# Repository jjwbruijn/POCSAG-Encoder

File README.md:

POCSAG-Encoder
==============
For more info, see http://jelmerbruijn.nl/pocsag-encoder/

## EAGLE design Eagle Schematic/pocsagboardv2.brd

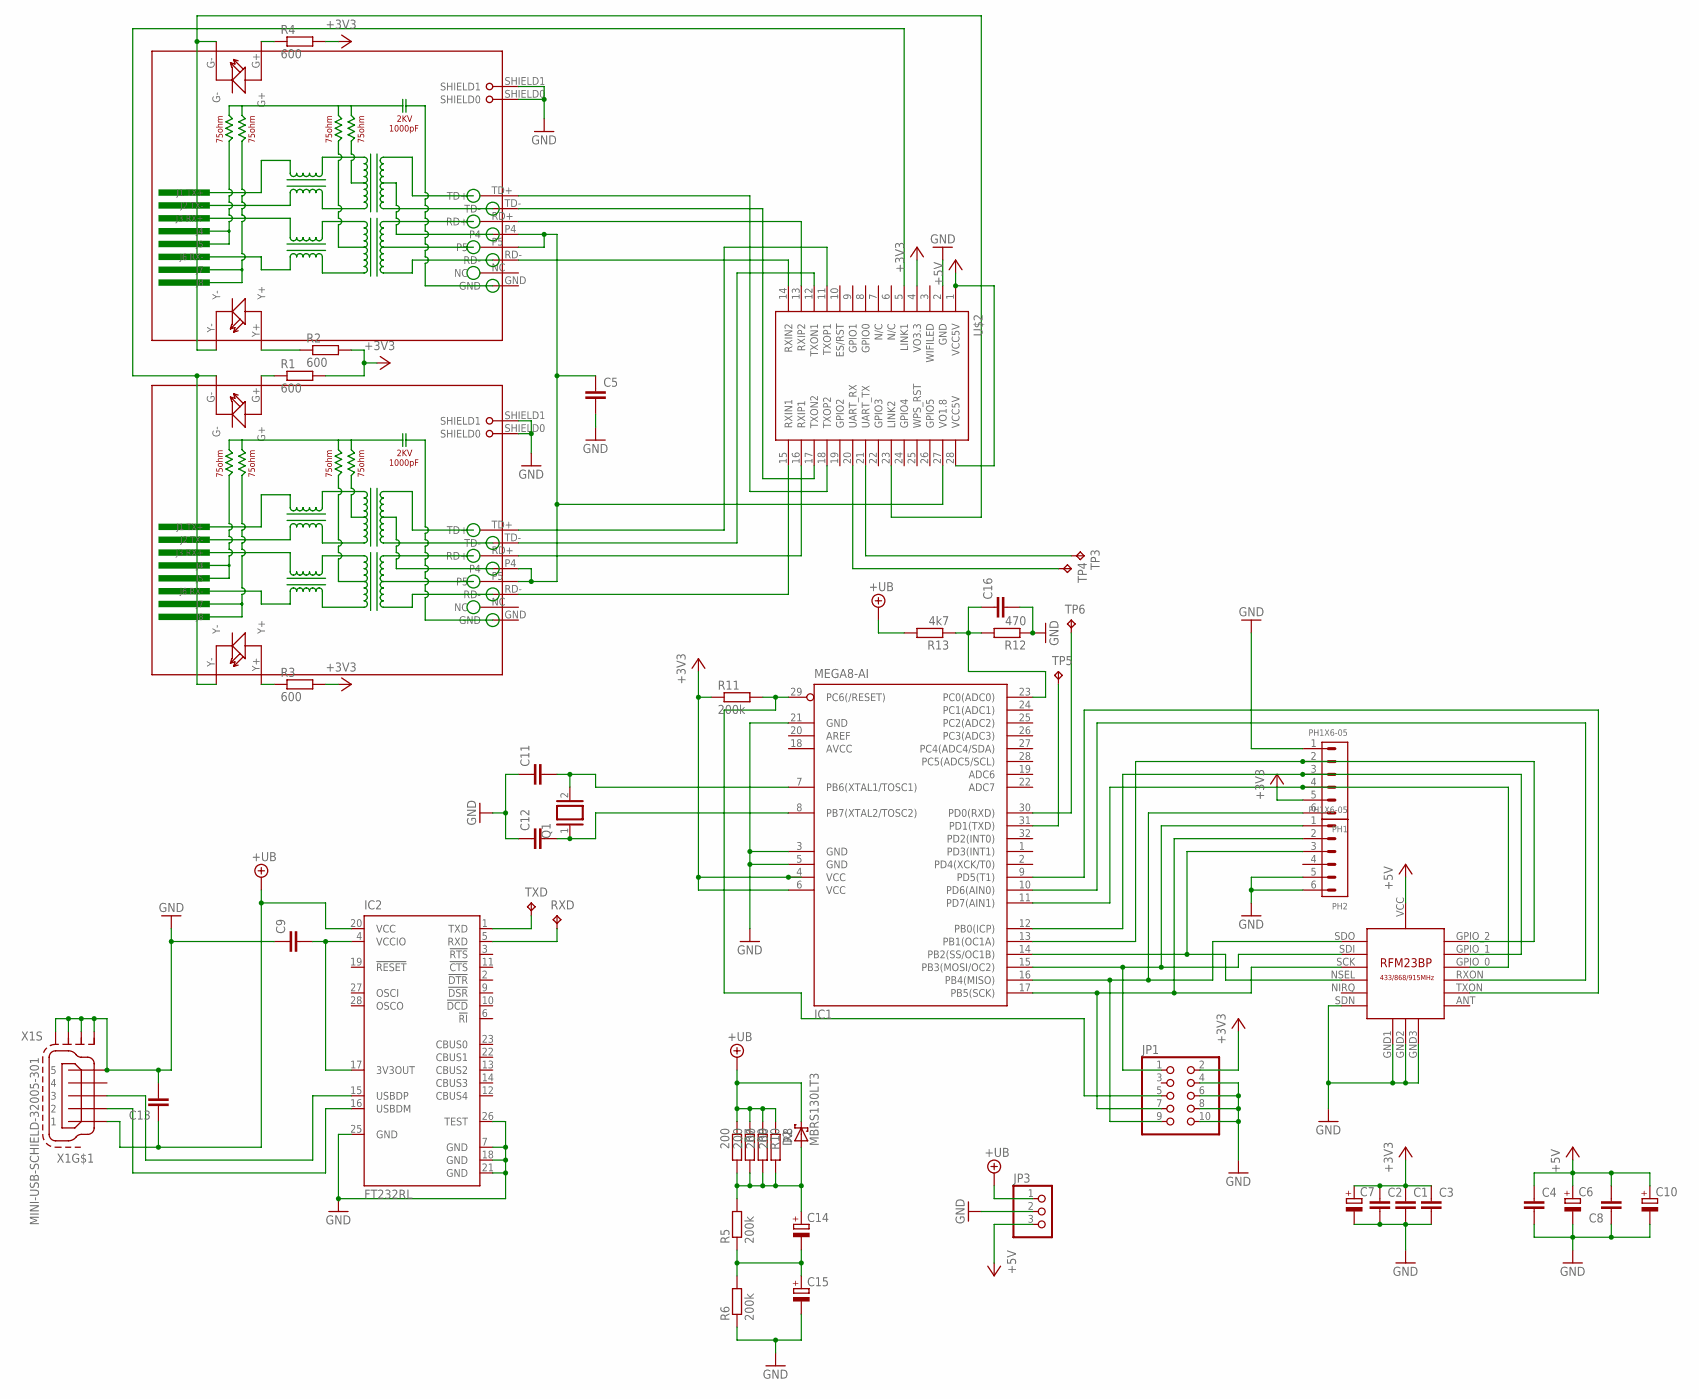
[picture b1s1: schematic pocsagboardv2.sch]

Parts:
C1, C2, C3, C4, C5, C8, C9, C13, C16: C-EUC1206K; C1206K
C6, C7, C10: CPOL-EU175TMP-0808; 175TMP-0808
C11, C12: C-EUC0805; C0805
C14, C15: CPOL-EUSANYO_F; SANYO-OSCON_F
D2: MBRS130LT3; SMB
IC1: MEGA8-AI; TQFP32-08
IC2: FT232RL; SSOP28
JP1: PINHD-2X5; 2X05
JP3: PINHD-1X3; 1X03
PH1, PH2: PH1X6-05; PH005-1-6
Q1: XTAL/S; QS
R1, R2, R3, R4: 600; M1206
R5, R6, R11: 200k; R1206
R7, R8, R9, R10: 200; R1206
R12: 470; R1206
R13: 4k7; R1206
RJ1, RJ2: HR911105A
RXD: TPTP10SQ; TP10SQ
TP3, TP4, TP5, TP6: TPTP10SQ; TP10SQ
TXD: TPTP10SQ; TP10SQ
U$1: RFM23BP
U$2: HLK-RM04
X1: MINI-USB-SCHIELD-32005-301; 32005-301

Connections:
+3V3: C1.1, C2.1, C3.1, C7.+, IC1.4 (VCC), IC1.6 (VCC), JP1.2, PH1.5, R1.2, R2.2, R3.2, R4.2, R11.1, U$2.4 (VO3.3)
+5V: C4.1, C6.+, C8.2, C10.+, JP3.3, U$1.VCC, U$2.1 (VCC5V), U$2.28 (VCC5V)
+UB: C13.1, D2.C, IC2.20 (VCC), JP3.1, R7.1, R8.1, R9.1, R10.1, R13.2, X1.1
AVCC: IC1.18 (AVCC)
GND: C1.2, C2.2, C3.2, C4.2, C5.2, C6.-, C7.-, C8.1, C9.1, C10.-, C11.1, C12.1, C13.2, C15.-, C16.2, IC1.3 (GND), IC1.5 (GND), IC1.21 (GND), IC2.7 (GND), IC2.18 (GND), IC2.21 (GND), IC2.25 (GND), IC2.26 (TEST), JP1.4, JP1.6, JP1.8, JP1.10, JP3.2, PH1.1, PH2.5, PH2.6, R6.1, R12.1, RJ1.SHIELD0, RJ1.SHIELD1, RJ2.SHIELD0, RJ2.SHIELD1, U$1.GND1, U$1.GND2, U$1.GND3, U$1.SDN, U$2.2 (GND), X1.5, X1.M1 (S1), X1.M2 (S2), X1.M3 (S3), X1.M4 (S4)
unnamed: IC1.11 (PD7(AIN1)), PH1.4, U$1.GPIO_0
unnamed: IC1.14 (PB2(SS/OC1B)), PH2.3, U$1.NSEL
unnamed: IC1.16 (PB4(MISO)), JP1.9, PH1.6, U$1.SDO
unnamed: IC1.15 (PB3(MOSI/OC2)), JP1.1, PH2.1, U$1.SDI
unnamed: IC1.17 (PB5(SCK)), JP1.7, PH2.2, U$1.SCK
unnamed: TP3.TP, U$2.21 (UART_TX)
unnamed: IC1.12 (PB0(ICP)), PH1.3, U$1.GPIO_1
unnamed: IC1.13 (PB1(OC1A)), PH1.2, U$1.GPIO_2
unnamed: IC1.10 (PD6(AIN0)), U$1.RXON
unnamed: IC1.9 (PD5(T1)), U$1.TXON
unnamed: TP4.TP, U$2.20 (UART_RX)
unnamed: RJ2.RD-, U$2.14 (RXIN2)
unnamed: RJ2.RD+, U$2.13 (RXIP2)
unnamed: RJ2.TD-, U$2.17 (TXON2)
unnamed: RJ2.TD+, U$2.18 (TXOP2)
unnamed: RJ1.TD-, U$2.12 (TXON1)
unnamed: RJ1.TD+, U$2.11 (TXOP1)
unnamed: RJ1.RD+, U$2.16 (RXIP1)
unnamed: RJ1.RD-, U$2.15 (RXIN1)
unnamed: R1.1, RJ1.G+
unnamed: C5.1, RJ1.P4, RJ1.P5, RJ2.P4, RJ2.P5, U$2.27 (VO1.8)
unnamed: R2.1, RJ2.Y+
unnamed: R4.1, RJ2.G+
unnamed: R3.1, RJ1.Y+
unnamed: RJ2.G-, RJ2.Y-, U$2.23 (LINK2)
unnamed: RJ1.G-, RJ1.Y-, U$2.5 (LINK1)
unnamed: IC2.16 (USBDM), X1.2
unnamed: C11.2, IC1.7 (PB6(XTAL1/TOSC1)), Q1.2
unnamed: IC2.15 (USBDP), X1.3
unnamed: C9.2, IC2.4 (VCCIO), IC2.17 (3V3OUT)
unnamed: IC1.30 (PD0(RXD)), TP6.TP
unnamed: IC2.1 (TXD), TXD.TP
unnamed: IC1.31 (PD1(TXD)), TP5.TP
unnamed: IC2.5 (RXD), RXD.TP
unnamed: C16.1, IC1.23 (PC0(ADC0)), R12.2, R13.1
unnamed: IC1.29 (PC6(/RESET)), JP1.5, R11.2
unnamed: C12.2, IC1.8 (PB7(XTAL2/TOSC2)), Q1.1
unnamed: C14.-, C15.+, R5.1, R6.2
unnamed: C14.+, D2.A, R5.2, R7.2, R8.2, R9.2, R10.2

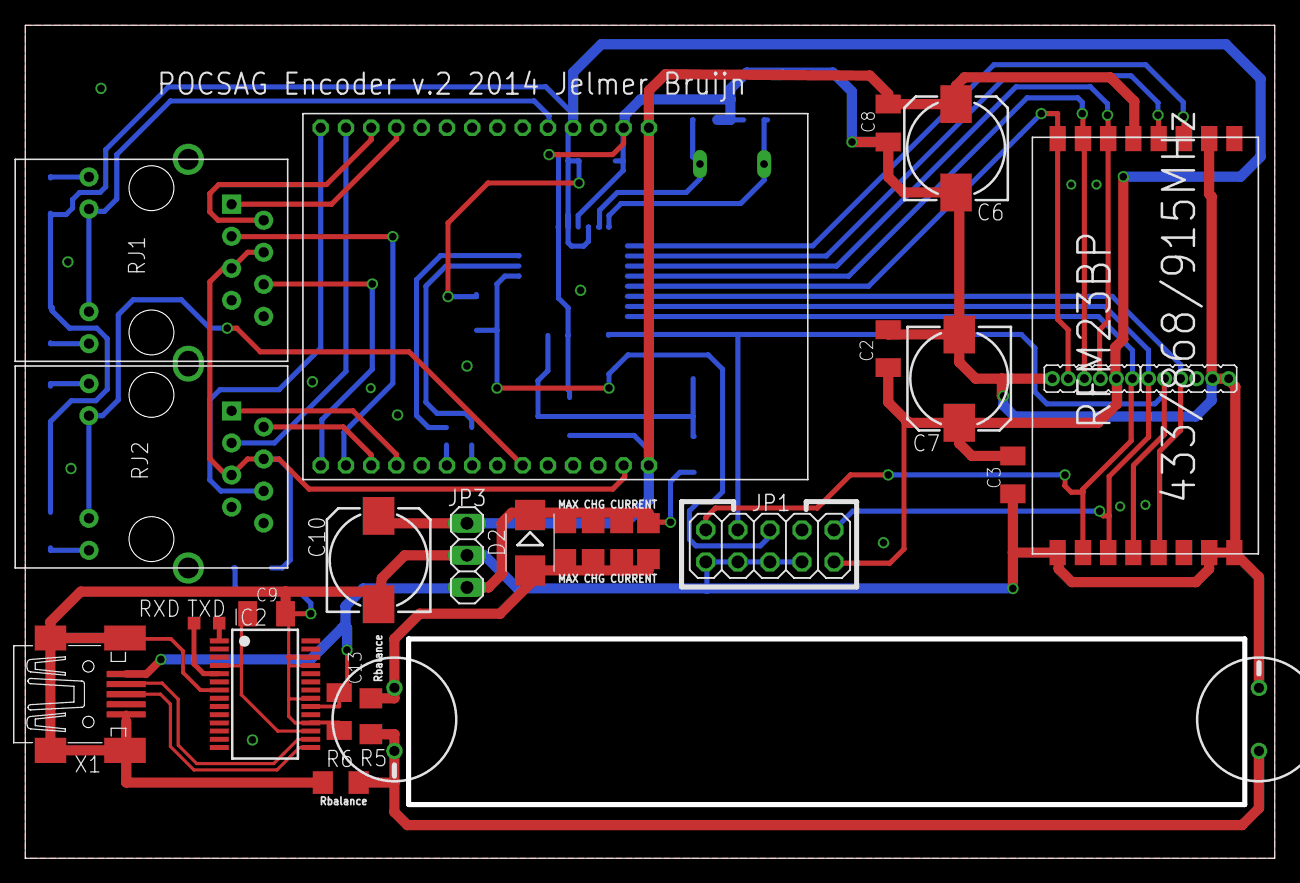
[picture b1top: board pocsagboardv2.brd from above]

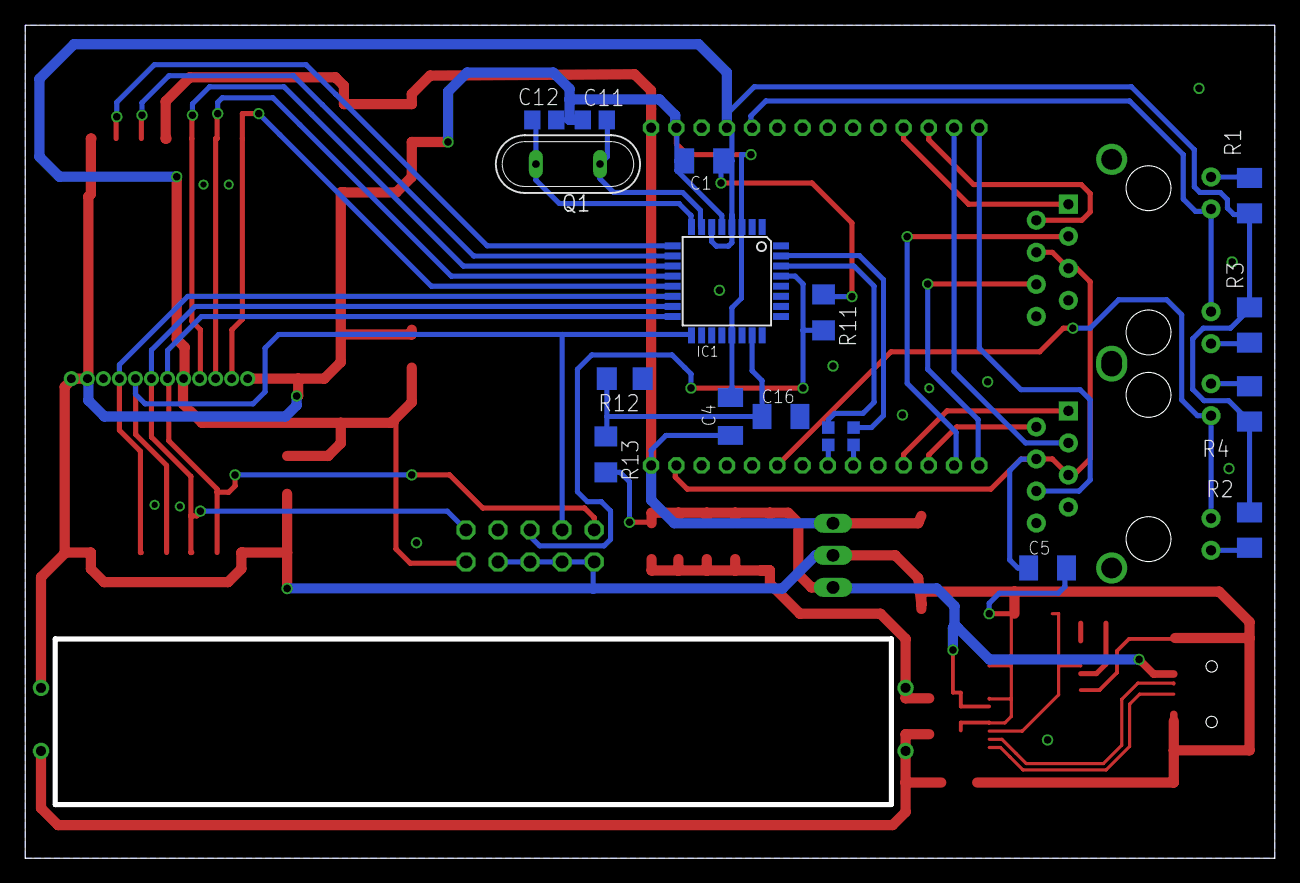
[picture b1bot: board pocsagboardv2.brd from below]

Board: 2 copper layers, 98.6 x 65.6 mm, 48 parts (19 on the bottom side), 43 nets.

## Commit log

2014-12-15 Initial commit schematics
2014-12-15 Initial AVR Code commit
2014-12-15 PHP Syslog Demo Initial Commit
